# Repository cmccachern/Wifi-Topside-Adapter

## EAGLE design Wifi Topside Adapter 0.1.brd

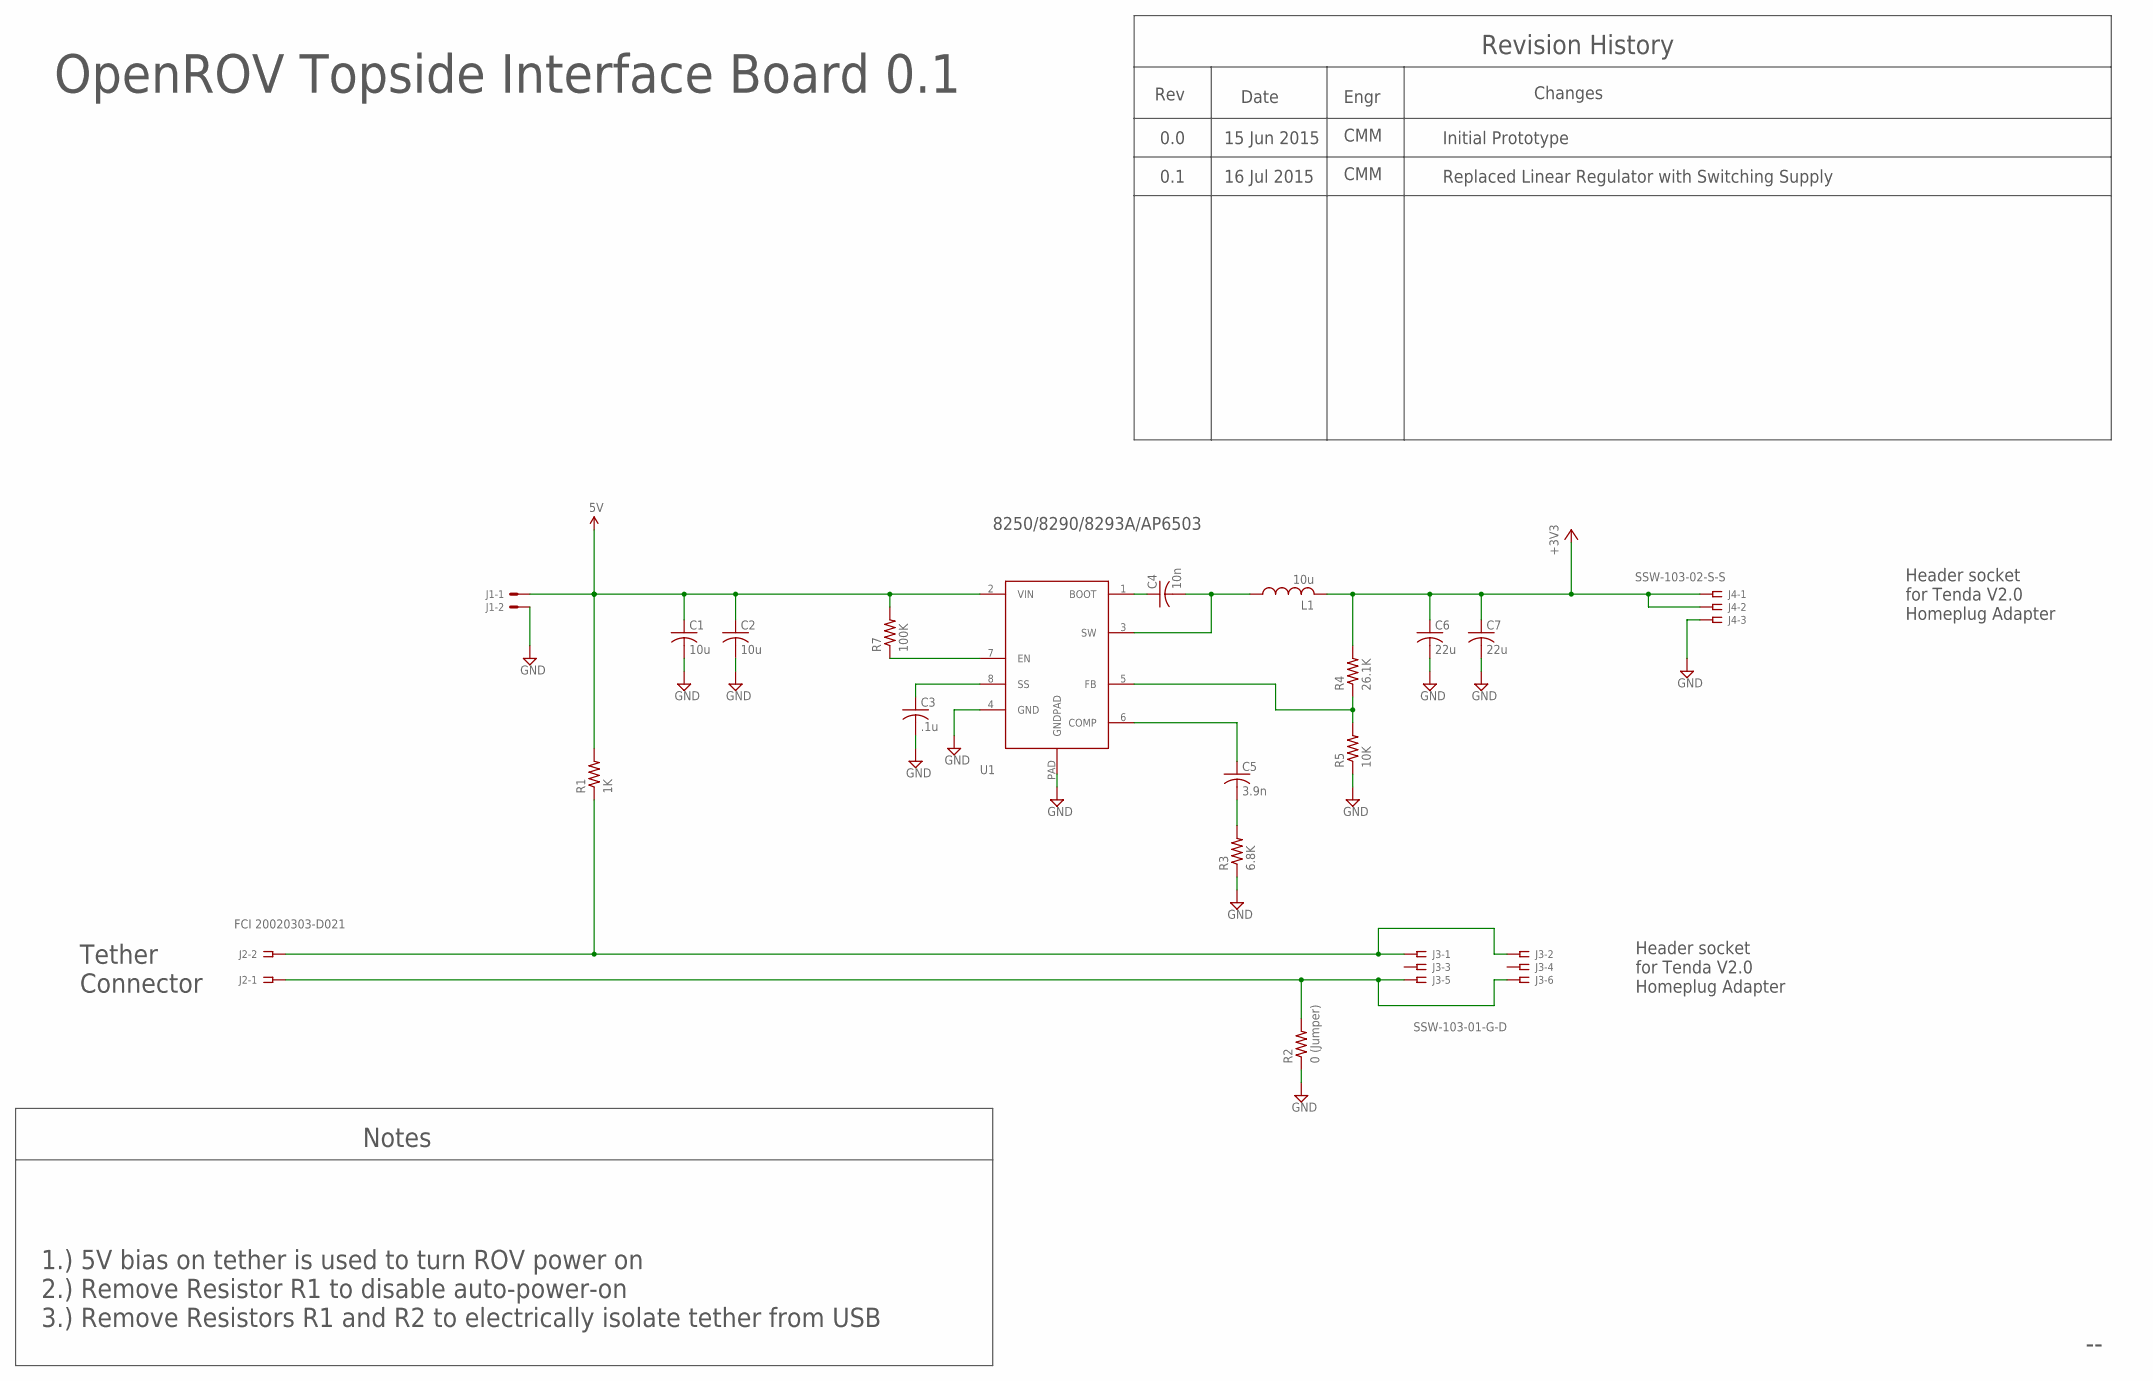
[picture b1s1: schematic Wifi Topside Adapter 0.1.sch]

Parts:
C1, C2: 10u; R1206
C3: .1u; R0805
C4: 10n; R0805
C5: 3.9n; R0805
C6, C7: 22u; R1206
J1: HDR_1X2X0.100-ALT_SILK; 22-23-2021_ALT_SILK
J2: FCI 20020303-D021; FCI_09-381_2PL
J3: SSW-103-01-G-D; SSW-103-02-S-D
J4: SSW-103-02-S-S
L1: 10u; INDUCTOR_3A_TEST
R1: 1K; R0805
R2: 0 (Jumper); R0805
R3: 6.8K; R0805
R4: 26.1K; R0805
R5: 10K; R0805
R7: 100K; R0805
U1: RICHTEK_82XX; SO8-THERMAL

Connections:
5V: C1.1, C2.1, J1.1, R1.2, R7.2, U1.2 (VIN)
+3V3: C6.1, C7.1, J4.1, J4.2, L1.P$2 (2), R4.2
GND: C1.2, C2.2, C3.2, C6.2, C7.2, J1.2, J4.3, R2.1, R3.1, R5.1, U1.4 (GND), U1.PAD (GNDPAD)
unnamed: J2.1A, J2.1B, J3.5, J3.6, R2.2
unnamed: J2.2A, J2.2B, J3.1, J3.2, R1.1
unnamed: C3.1, U1.8 (SS)
unnamed: C5.1, U1.6 (COMP)
unnamed: C5.2, R3.2
unnamed: R4.1, R5.2, U1.5 (FB)
unnamed: C4.1, U1.1 (BOOT)
unnamed: R7.1, U1.7 (EN)
unnamed: C4.2, L1.P$1 (1), U1.3 (SW)

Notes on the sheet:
Revision History
Rev
Date
Changes
0.0
15 Jun 2015
Initial Prototype
Engr
CMM
OpenROV Topside Interface Board 0.1
Tether Connector
Header socket for Tenda V2.0 Homeplug Adapter
Notes
1.) 5V bias on tether is used to turn ROV power on 2.) Remove Resistor R1 to disable auto-power-on 3.) Remove Resistors R1 and R2 to electrically isolate tether from USB
8250/8290/8293A/AP6503
0.1
16 Jul 2015
Replaced Linear Regulator with Switching Supply

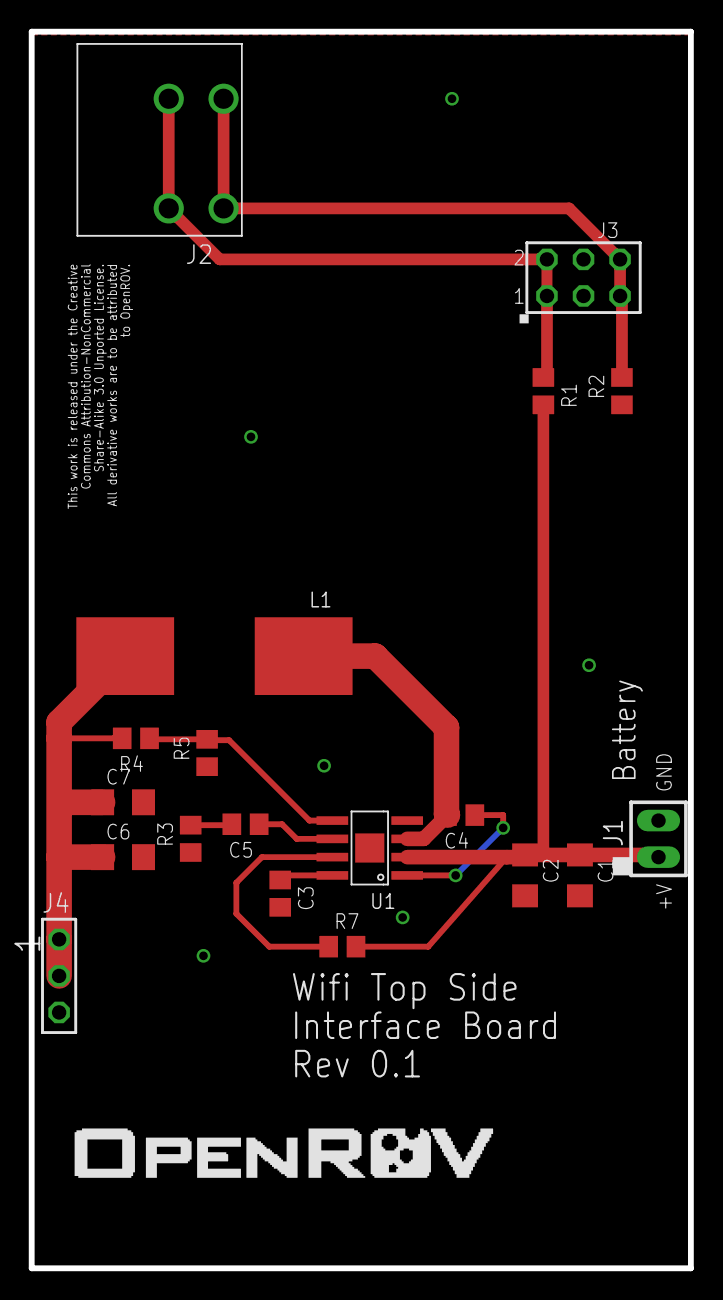
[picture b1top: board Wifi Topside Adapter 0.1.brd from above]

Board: 2 copper layers, 45.8 x 85.9 mm, 19 parts (0 on the bottom side), 12 nets.

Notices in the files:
parts and their libraries:
OpenROV General Library: This work is released under the Creative Commons
Attribution-NonCommercial-Share Alike 3.0
SparkFun-Aesthetics: Licensing: CC v3.0 Share-Alike You are welcome to use this library for commercial purposes.
